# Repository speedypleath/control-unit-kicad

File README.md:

# Haptic Console — Control Unit (M6) KiCad Project

KiCad project for the Control Unit module of the Haptic Console v1.0. One schematic,
two PCBs: a compact manufactured board (SMD, routed, ready for fab) and a hand-wireable
perfboard build.

## Schematic

U1 Teensy 4.1, S1–S6 haptic driver connectors (6-pin JST-XH, [XH2.54 v1.1 standard](#connector-standard)),
B1–B8 tactile buttons, CB1–CB5 + R1–R5 LED/button conditioning, R12/R13 I²C pull-ups,
J1/J2 joystick headers, NP1 numpad matrix, TP1–TP5 test points (SDA/SCL/GND/+3V3/+5V,
tapped at the I²C pull-up network). ERC: 0 errors/0 warnings.

## Manufactured board

Compact (88×131mm) layout, SMD 0603 resistors, fully autorouted (654 track segments,
35 vias, 0 unrouted nets), plus 5 THT test-point pads (TP1–TP5) for SDA/SCL/GND/+3V3/+5V
near R12/R13. DRC: 0 errors/0 warnings, 0 unconnected pads.

Gerbers + drill file: [`project/haptic-console-control-unit-gerbers.zip`](project/haptic-console-control-unit-gerbers.zip)
(Gerber X2 + Excellon drill, plain KiCad-default output — no fab-specific renaming).
View with [gerbv](https://gerbv.github.io/) or unzip and drag into your fab's order-check
tool (JLCPCB/PCBWay/OSH Park all accept the zip directly).

## Perfboard build

Hand-wireable 90×150mm 32×50-hole perfboard layout, same schematic/nets, laid out for
row/column GND+3V3+5V+SDA+SCL bus wiring, with 223 colour-coded back-side jumper wires
modelled in 3D (see [`docs/perfboard-wiring-regeneration.md`](docs/perfboard-wiring-regeneration.md)). TP1–TP5 are real male 2.54mm header pins
(not just pads) in the last column at the board's right edge, past S6 — clip a jumper
or scope hook straight on instead of back-probing a live JST connector. Full
per-connector wiring plan (every connection as a board grid reference, e.g.
`S1.1 → Q23`), live at
**[wiring-guide](https://speedypleath.github.io/control-unit-kicad/wiring-guide.html)**
(source: [`docs/wiring-guide.html`](docs/wiring-guide.html)). Print
[`renders/perfboard-placement-template-1to1.pdf`](renders/perfboard-placement-template-1to1.pdf)
at 100%/Actual Size for physical placement.

## GPIO assignment

Every connector signal is wired to whichever Teensy digital pin sits physically closest
to it, rather than to a contiguous block per function — 1356 mm of Manhattan run in total,
longest single wire 61 mm, 223 modelled jumper legs on the perfboard. The assignments are
therefore **not** sequential; the authoritative map is `scripts/pin_map.json`, rendered per
connector in the [wiring guide](docs/wiring-guide.html) and the
[panel wiring guide](docs/panel-wiring-guide.html). Firmware pin constants must follow
that map.

Eighteen conductors are **frozen** because they are already soldered on the built board and
are an input to the solver, not a result: B1–B8, both joysticks (J1/J2), and the LED4/LED5
lamp jumpers. Everything else — the six module IRQs, the five control-button switches, the
other three lamps and the eight numpad lines — is re-solved for proximity whenever the
layout moves. The Teensy plugs in **USB toward the `B23`/`B29` end**; if that is ever in
doubt, settle it by reading a hole off the physical board, never by checking whether the
resulting map looks sensible.

## Connector standard

S1–S6 haptic-module cables follow **XH2.54 6-pin — Haptic Console Connector Standard
v1.1**: pin 1 GND, pin 2 3.3V, pin 3 5V, pin 4 SDA, pin 5 SCL, pin 6 IRQ.

## Libraries

- `teensy.pretty` / `teensy.kicad_sym` — XenGi Teensy 4.1 footprint + symbol (not stock
  KiCad), vendored in `libraries/`.
- `Connector_JST`, `Resistor_THT`, `Resistor_SMD`, `Device`, `Connector_Generic`, `power`
  — stock KiCad 10 libraries.
- `digikey-kicad-library`, `SparkFun-KiCad-Libraries` — additional atomic parts.
- Project `fp-lib-table` / `sym-lib-table` wired for all of the above.

## Files

- `project/` — schematic, both boards, project files, lib tables, `gerbers/` +
  `*-gerbers.zip` (manufactured board fab output)
- `libraries/` — vendored XenGi `teensy.pretty`
- `renders/` — schematic + PCB renders
- `docs/` — wiring guide, build log, kicad-mcp lessons

## Sources

- Teensy 4.1 footprints: https://github.com/XenGi/teensy.pretty
- Digi-Key atomic parts: https://github.com/Digi-Key/digikey-kicad-library
- SparkFun: https://github.com/sparkfun/SparkFun-KiCad-Libraries
- KiCad stock footprints: https://gitlab.com/kicad/libraries/kicad-footprints

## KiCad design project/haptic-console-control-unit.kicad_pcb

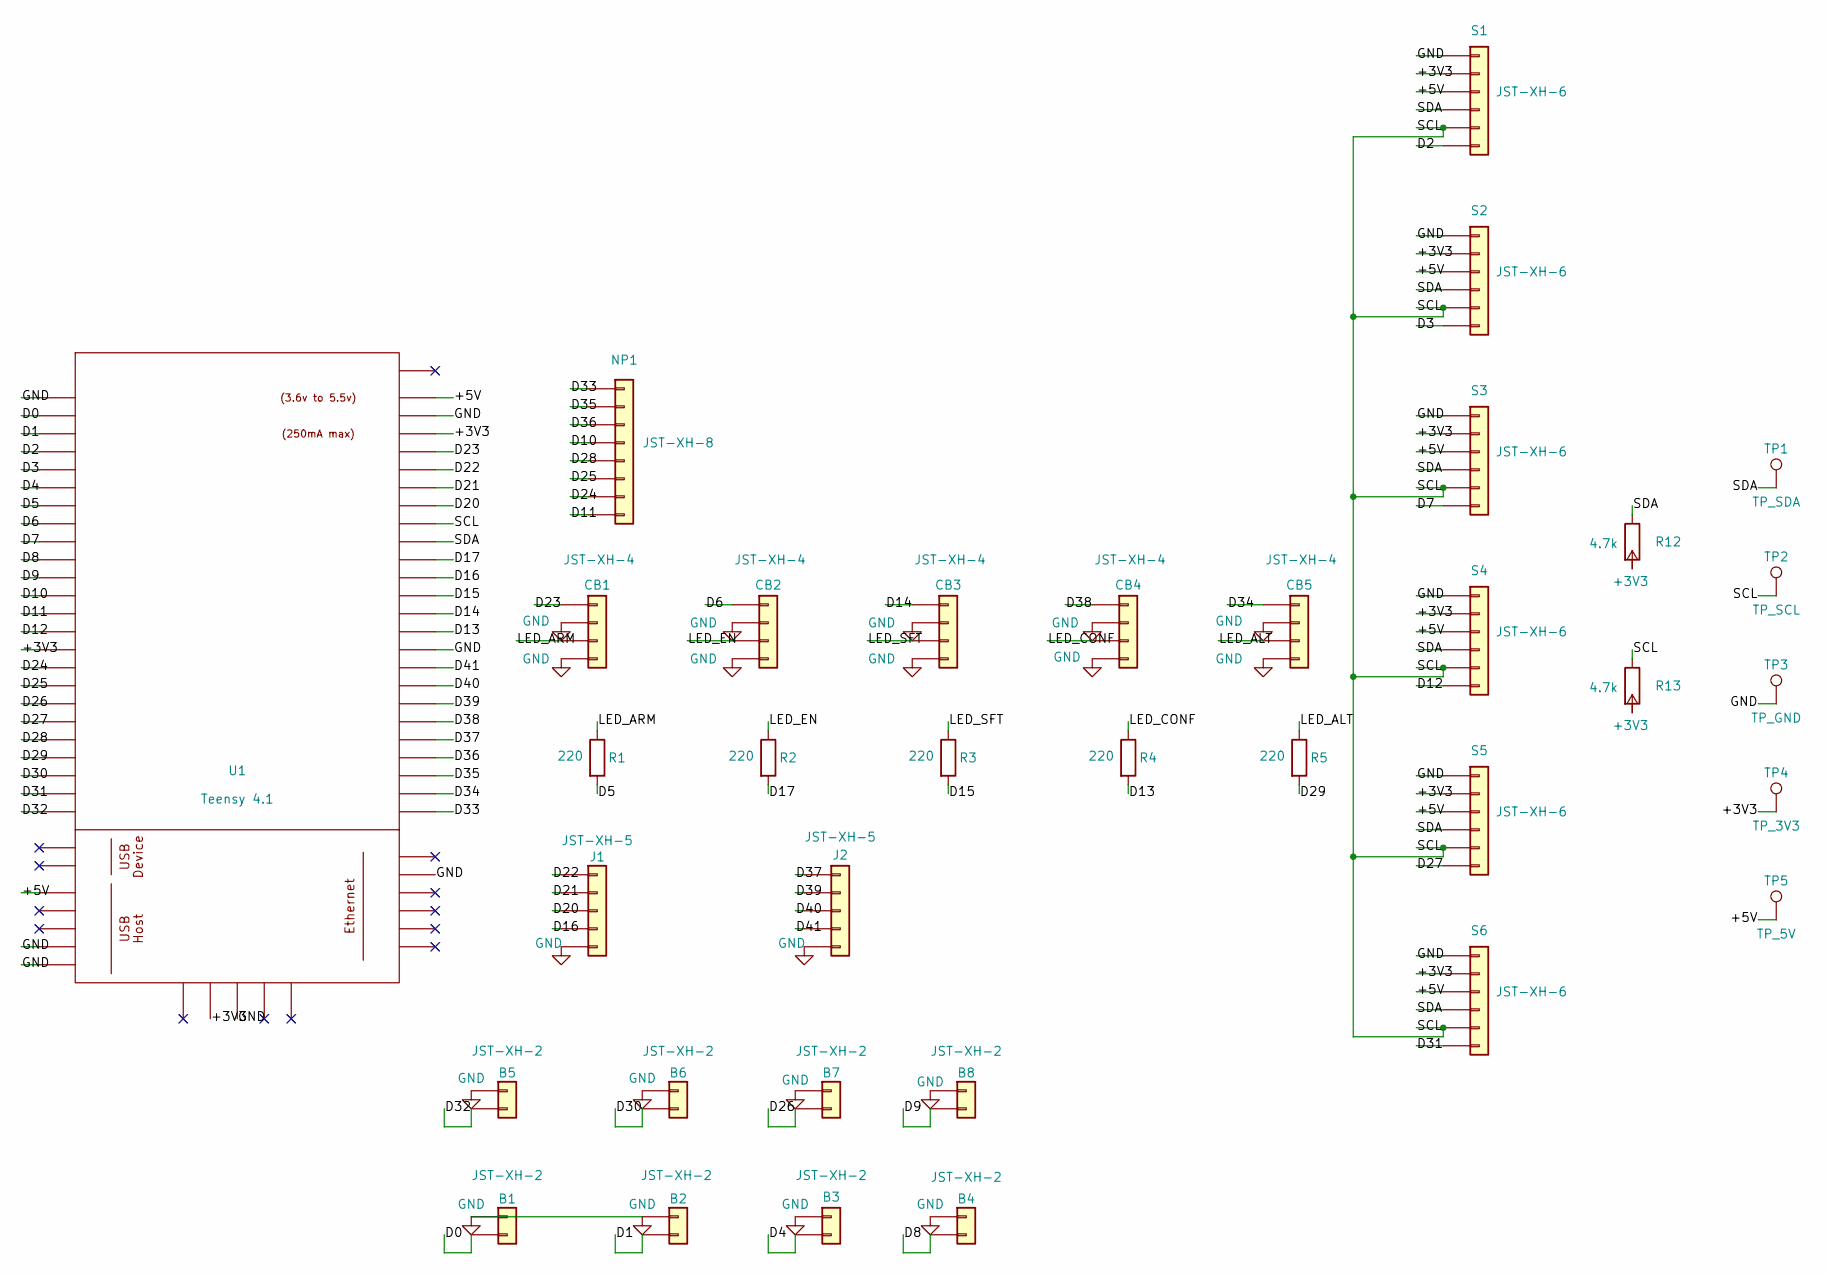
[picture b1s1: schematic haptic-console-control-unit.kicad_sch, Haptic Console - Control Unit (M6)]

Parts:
B1, B2, B3, B4, B5, B6, B7, B8: JST-XH-2; JST_XH_B2B-XH-A_1x02_P2.50mm_Vertical
CB1, CB2, CB3, CB4, CB5: JST-XH-4; JST_XH_B4B-XH-A_1x04_P2.50mm_Vertical
J1, J2: JST-XH-5; JST_XH_B5B-XH-A_1x05_P2.50mm_Vertical
NP1: JST-XH-8; JST_XH_B8B-XH-A_1x08_P2.50mm_Vertical
R1, R2, R3, R4, R5: 220; R_Axial_DIN0207_L6.3mm_D2.5mm_P10.16mm_Horizontal
R12, R13: 4.7k; R_Axial_DIN0207_L6.3mm_D2.5mm_P10.16mm_Horizontal
S1, S2, S3, S4, S5, S6: JST-XH-6; JST_XH_B6B-XH-A_1x06_P2.50mm_Vertical
TP1: TP_SDA; TestPoint_THTPad_D1.5mm_Drill0.7mm
TP2: TP_SCL; TestPoint_THTPad_D1.5mm_Drill0.7mm
TP3: TP_GND; TestPoint_THTPad_D1.5mm_Drill0.7mm
TP4: TP_3V3; TestPoint_THTPad_D1.5mm_Drill0.7mm
TP5: TP_5V; TestPoint_THTPad_D1.5mm_Drill0.7mm
U1: Teensy 4.1; Teensy41

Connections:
+3V3: R12.2, R13.2, S1.2, S2.2, S3.2, S4.2, S5.2, S6.2, TP4.1, U1.15 (3V3), U1.46 (3V3), U1.51 (3V3)
/+5V: S1.3, S2.3, S3.3, S4.3, S5.3, S6.3, TP5.1, U1.48 (VIN), U1.55 (5V)
/D0: B1.2, U1.2 (0_RX1_CRX2_CS1)
/D1: B2.2, U1.3 (1_TX1_CTX2_MISO1)
/D2: S1.6, U1.4 (2_OUT2)
/D3: S2.6, U1.5 (3_LRCLK2)
/D4: B3.2, U1.6 (4_BCLK2)
/D5: R1.2, U1.7 (5_IN2)
/D6: CB2.1, U1.8 (6_OUT1D)
/D7: S3.6, U1.9 (7_RX2_OUT1A)
/D8: B4.2, U1.10 (8_TX2_IN1)
/D9: B8.2, U1.11 (9_OUT1C)
/D10: NP1.4, U1.12 (10_CS_MQSR)
/D11: NP1.8, U1.13 (11_MOSI_CTX1)
/D12: S4.6, U1.14 (12_MISO_MQSL)
/D13: R4.2, U1.35 (13_SCK_LED)
/D14: CB3.1, U1.36 (14_A0_TX3_SPDIF_OUT)
/D15: R3.2, U1.37 (15_A1_RX3_SPDIF_IN)
/D16: J1.4, U1.38 (16_A2_RX4_SCL1)
/D17: R2.2, U1.39 (17_A3_TX4_SDA1)
/D20: J1.3, U1.42 (20_A6_TX5_LRCLK1)
/D21: J1.2, U1.43 (21_A7_RX5_BCLK1)
/D22: J1.1, U1.44 (22_A8_CTX1)
/D23: CB1.1, U1.45 (23_A9_CRX1_MCLK1)
/D24: NP1.7, U1.16 (24_A10_TX6_SCL2)
/D25: NP1.6, U1.17 (25_A11_RX6_SDA2)
/D26: B7.2, U1.18 (26_A12_MOSI1)
/D27: S5.6, U1.19 (27_A13_SCK1)
/D28: NP1.5, U1.20 (28_RX7)
/D29: R5.2, U1.21 (29_TX7)
/D30: B6.2, U1.22 (30_CRX3)
/D31: S6.6, U1.23 (31_CTX3)
/D32: B5.2, U1.24 (32_OUT1B)
/D33: NP1.1, U1.25 (33_MCLK2)
/D34: CB5.1, U1.26 (34_RX8)
/D35: NP1.2, U1.27 (35_TX8)
/D36: NP1.3, U1.28 (36_CS)
/D37: J2.1, U1.29 (37_CS)
/D38: CB4.1, U1.30 (38_CS1_IN1)
/D39: J2.2, U1.31 (39_MISO1_OUT1A)
/D40: J2.3, U1.32 (40_A16)
/D41: J2.4, U1.33 (41_A17)
/LED_ALT: CB5.3, R5.1
/LED_ARM: CB1.3, R1.1
/LED_CONF: CB4.3, R4.1
/LED_EN: CB2.3, R2.1
/LED_SFT: CB3.3, R3.1
/SCL: R13.1, S1.5, S2.5, S3.5, S4.5, S5.5, S6.5, TP2.1, U1.41 (19_A5_SCL)
/SDA: R12.1, S1.4, S2.4, S3.4, S4.4, S5.4, S6.4, TP1.1, U1.40 (18_A4_SDA)
GND: B1.1, B2.1, B3.1, B4.1, B5.1, B6.1, B7.1, B8.1, CB1.2, CB1.4, CB2.2, CB2.4, CB3.2, CB3.4, CB4.2, CB4.4, CB5.2, CB5.4, J1.5, J2.5, S1.1, S2.1, S3.1, S4.1, S5.1, S6.1, TP3.1, U1.1 (GND), U1.34 (GND), U1.47 (GND), U1.52 (GND), U1.58 (GND), U1.59 (GND), U1.64 (GND)

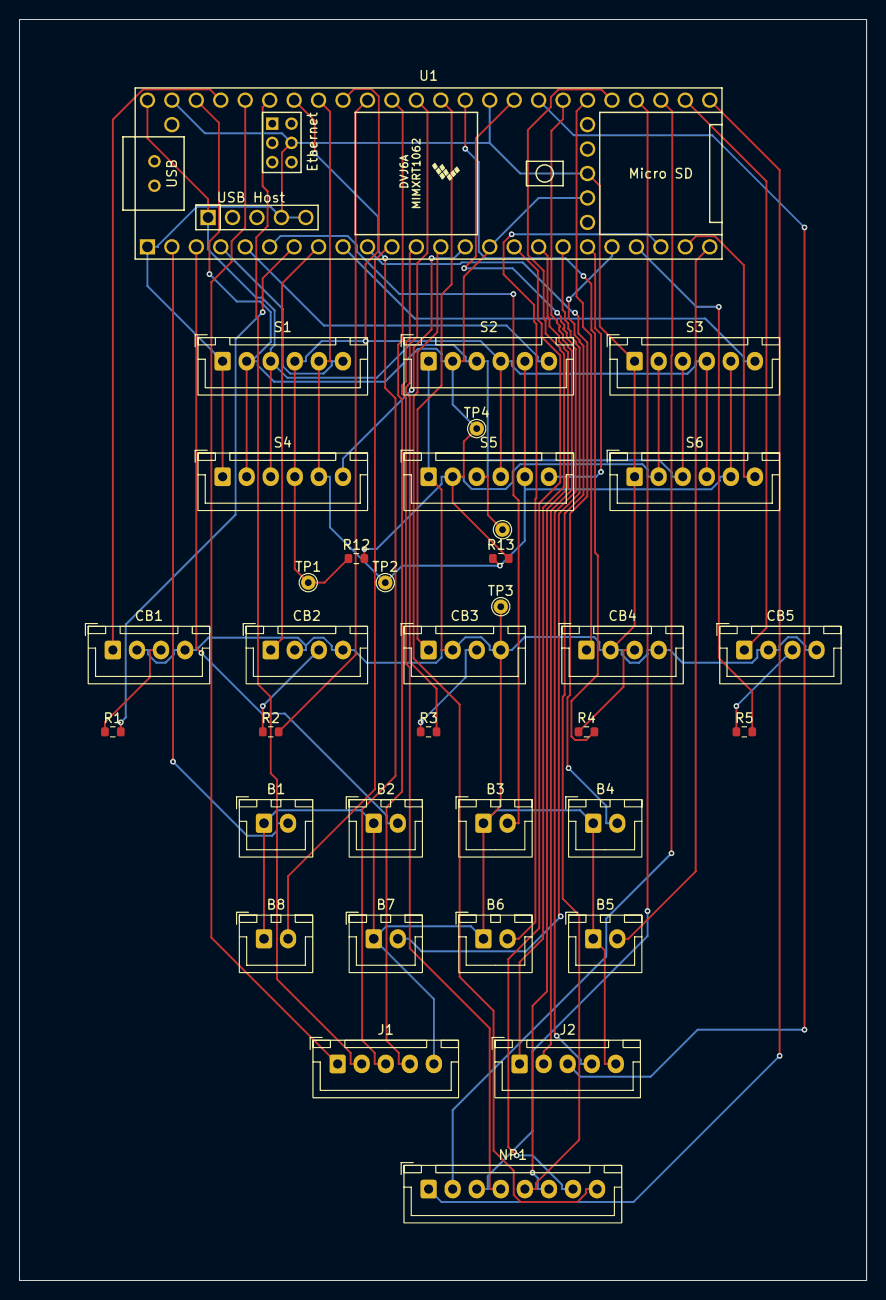
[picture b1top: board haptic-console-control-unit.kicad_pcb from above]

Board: 2 copper layers, 88.0 x 131.0 mm, 35 parts (0 on the bottom side), 50 nets.
